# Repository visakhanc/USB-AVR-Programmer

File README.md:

USB AVR Programmer
==================

USB AVR programmer PCB and firmware files. There is Eagle PCB files for two versions: One with 5V target voltage only, other with selectable 3.3V and 5V target supply voltage. There is also a single side PCB layout image, which is meant for homemade PCB making.

For flashing the firmware, use another AVR ISP programmer connected to the ISP socket. Read the instruction in the firmware folder.

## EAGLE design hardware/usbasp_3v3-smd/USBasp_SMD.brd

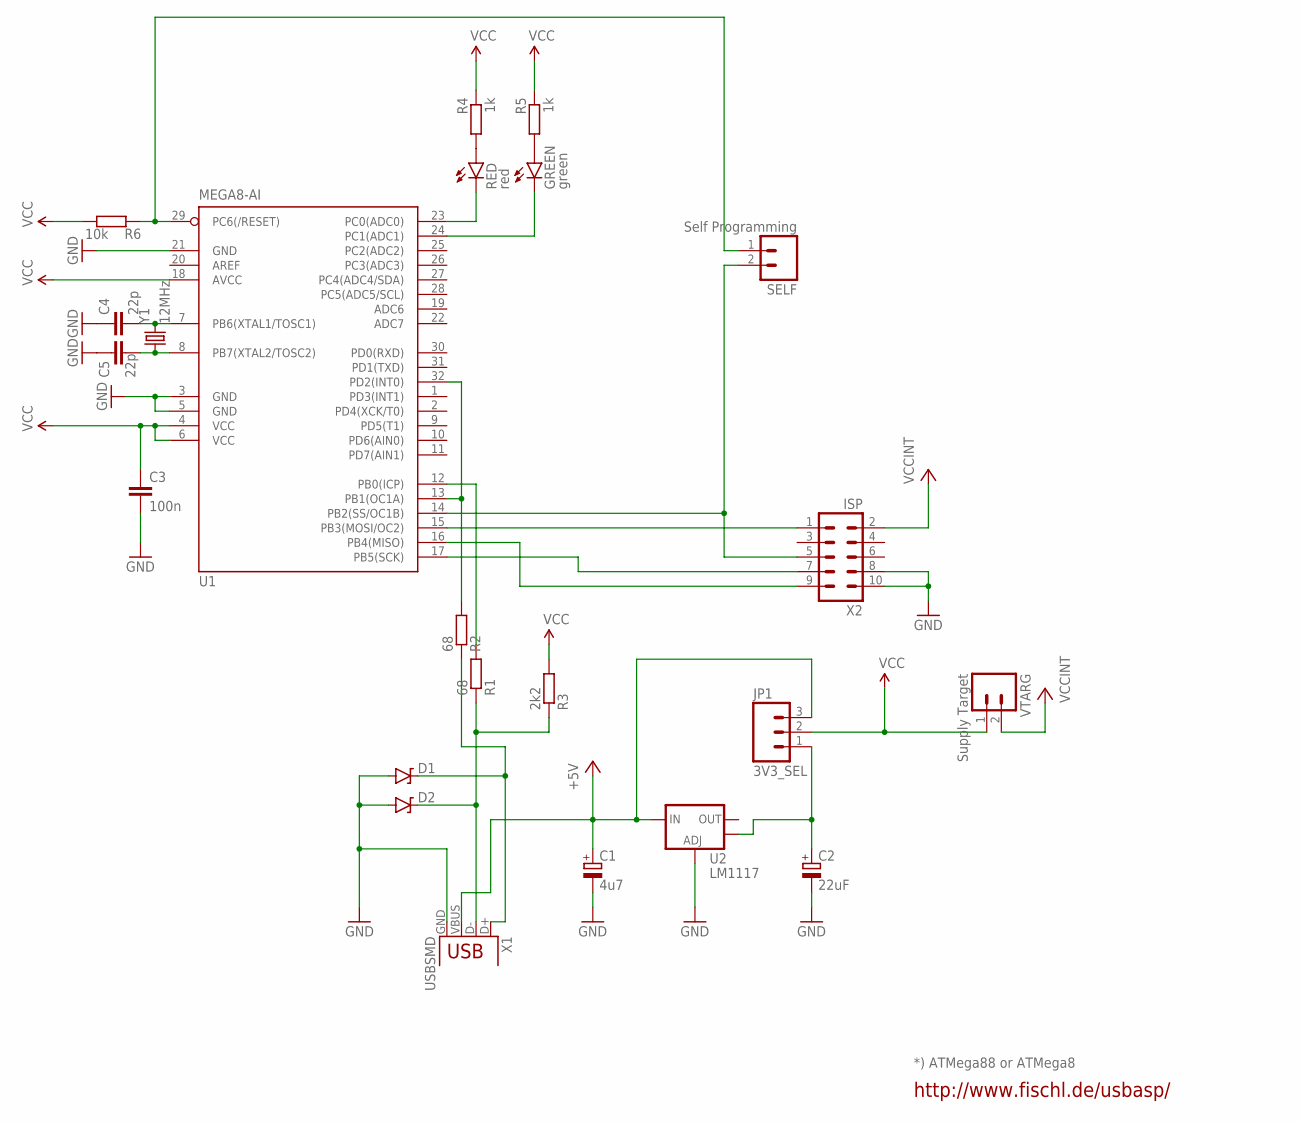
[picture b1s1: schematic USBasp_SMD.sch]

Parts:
C1: 4u7; E2,5-5
C2: 22uF; E2,5-5
C3: 100n; C1206
C4, C5: 22p; C1206
D1, D2: 3V6; DIODE-ZENER
GREEN: green; LED-1206
JP1: 3V3_SEL; 1X03
R1, R2: 68; M1206
R3: 2k2; M1206
R4, R5: 1k; M1206
R6: 10k; M1206
RED: red; LED-1206
SELF: Self Programming; 1X02
U1: MEGA8-AI; TQFP32-08
U2: LM1117; SOT223
VTARG: Supply Target; 1X02
X1: USBSMD; USB-MINIB
X2: ISP; ML10L
Y1: 12MHz; HC49UP

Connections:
+5V: C1.+, JP1.3, U2.3 (IN), X1.VBUS
GND: C1.-, C2.-, C3.2, C4.1, C5.1, D1.P$2 (A), D2.P$2 (A), U1.3 (GND), U1.5 (GND), U1.21 (GND), U2.1 (ADJ), X1.GND, X2.8, X2.10
unnamed: R6.2, SELF.1, U1.29 (PC6(/RESET))
unnamed: SELF.2, U1.14 (PB2(SS/OC1B)), X2.5
unnamed: U1.15 (PB3(MOSI/OC2)), X2.1
unnamed: U1.17 (PB5(SCK)), X2.7
unnamed: D2.P$1 (C), R1.1, R3.1, X1.D-
unnamed: U1.16 (PB4(MISO)), X2.9
unnamed: D1.P$1 (C), R2.1, X1.D+
unnamed: C2.+, JP1.1, U2.4 (OUT)
unnamed: R2.2, U1.13 (PB1(OC1A)), U1.32 (PD2(INT0))
unnamed: R1.2, U1.12 (PB0(ICP))
unnamed: R4.2, RED.A
unnamed: RED.C, U1.23 (PC0(ADC0))
unnamed: GREEN.C, U1.24 (PC1(ADC1))
unnamed: C4.2, U1.7 (PB6(XTAL1/TOSC1)), Y1.2
unnamed: C5.2, U1.8 (PB7(XTAL2/TOSC2)), Y1.1
unnamed: GREEN.A, R5.2
VCC: C3.1, JP1.2, R3.2, R4.1, R5.1, R6.1, U1.4 (VCC), U1.6 (VCC), U1.18 (AVCC), VTARG.1
VCCINT: VTARG.2, X2.2

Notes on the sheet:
http://www.fischl.de/usbasp/
*) ATMega88 or ATMega8

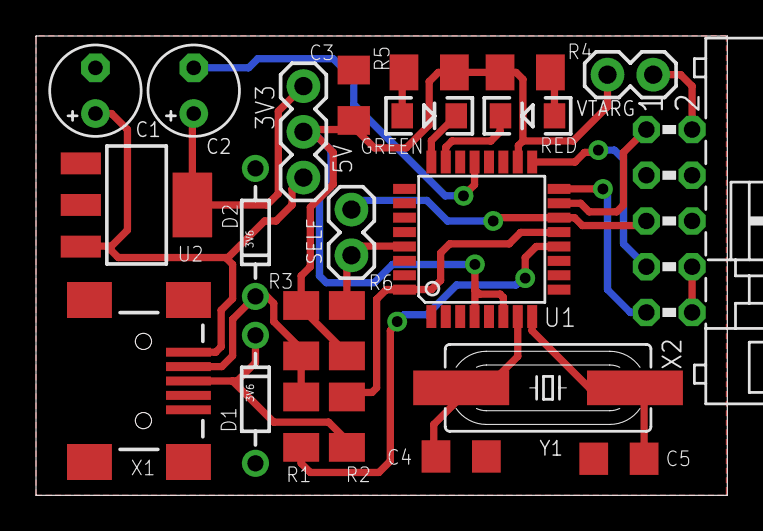
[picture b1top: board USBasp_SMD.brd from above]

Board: 2 copper layers, 38.4 x 25.5 mm, 23 parts (0 on the bottom side), 20 nets.

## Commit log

2017-03-16 Added README
2017-03-17 Added pics
2017-03-17 Added pictures
2017-03-17 Modified Readme

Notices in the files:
parts and their libraries:
SparkFun-FreqCtrl: Licensing: Creative Commons ShareAlike 4.0 International - https://creativecommons.org/licenses/by-sa/4.0
